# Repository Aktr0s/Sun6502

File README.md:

# Sun6502 Hobby Computer

## My first try at electonics. Wish me luck.

# Memory Map:

| Address Range   | Size   | Description        |
|-----------------|--------|--------------------|
| `$0000-$7FFF`   | 32KB   | RAM                |
| `$8000-$83FF`   | 1KB    | VIA #1             |
| `$8400-$87FF`   | 1KB    | UART               |
| `$8800-$8BFF`   | 1KB    | VIA #2             |
| `$8C00-$8FFF`   | 1KB    | Unused             |
| `$9000-$BFFF`   | 12KB   | Expansion Port     |
| `$C000-$FFFF`   | 16KB   | ROM                |

> **Total:** 64KB

> **If you have a previous version of the board notice that UART and VIA #2 addresses are swaped around.**

## More Info:
While VIA's and UART have 1KB they only use first needed bits.

VIA#2 Port (Expansion) does not have CE/ signal but Bus Expansion Port does.

It should be compatible with Ben's Breadboard 6502 but you **HAVE** to change memory adressess since the memory map is different as well as elements connected to VIA

### The project took inspiration from:
* Ben Eater Breadboard 6502 Computer
* PE6502 by Putnam Electronics

> [!NOTE]
> This project has been tested and is confirmed to work.

> [!CAUTION]
> Do NOT use 74LS series TTL chips. It messes up logic and memory.
> Use 74HC series CMOS chips! If somewhere on PCB or schematic there is a mention of TTL chips, ignore them and use CMOS chips!

## Software:

Software for this computer is based on 
* [msbasic](https://github.com/mist64/msbasic), licensed under the 2-clause BSD license.

* As well as it's modified version by [Ben Eater](https://github.com/beneater/msbasic).

Original README files are in "msbasic_for_sun6502" folder.

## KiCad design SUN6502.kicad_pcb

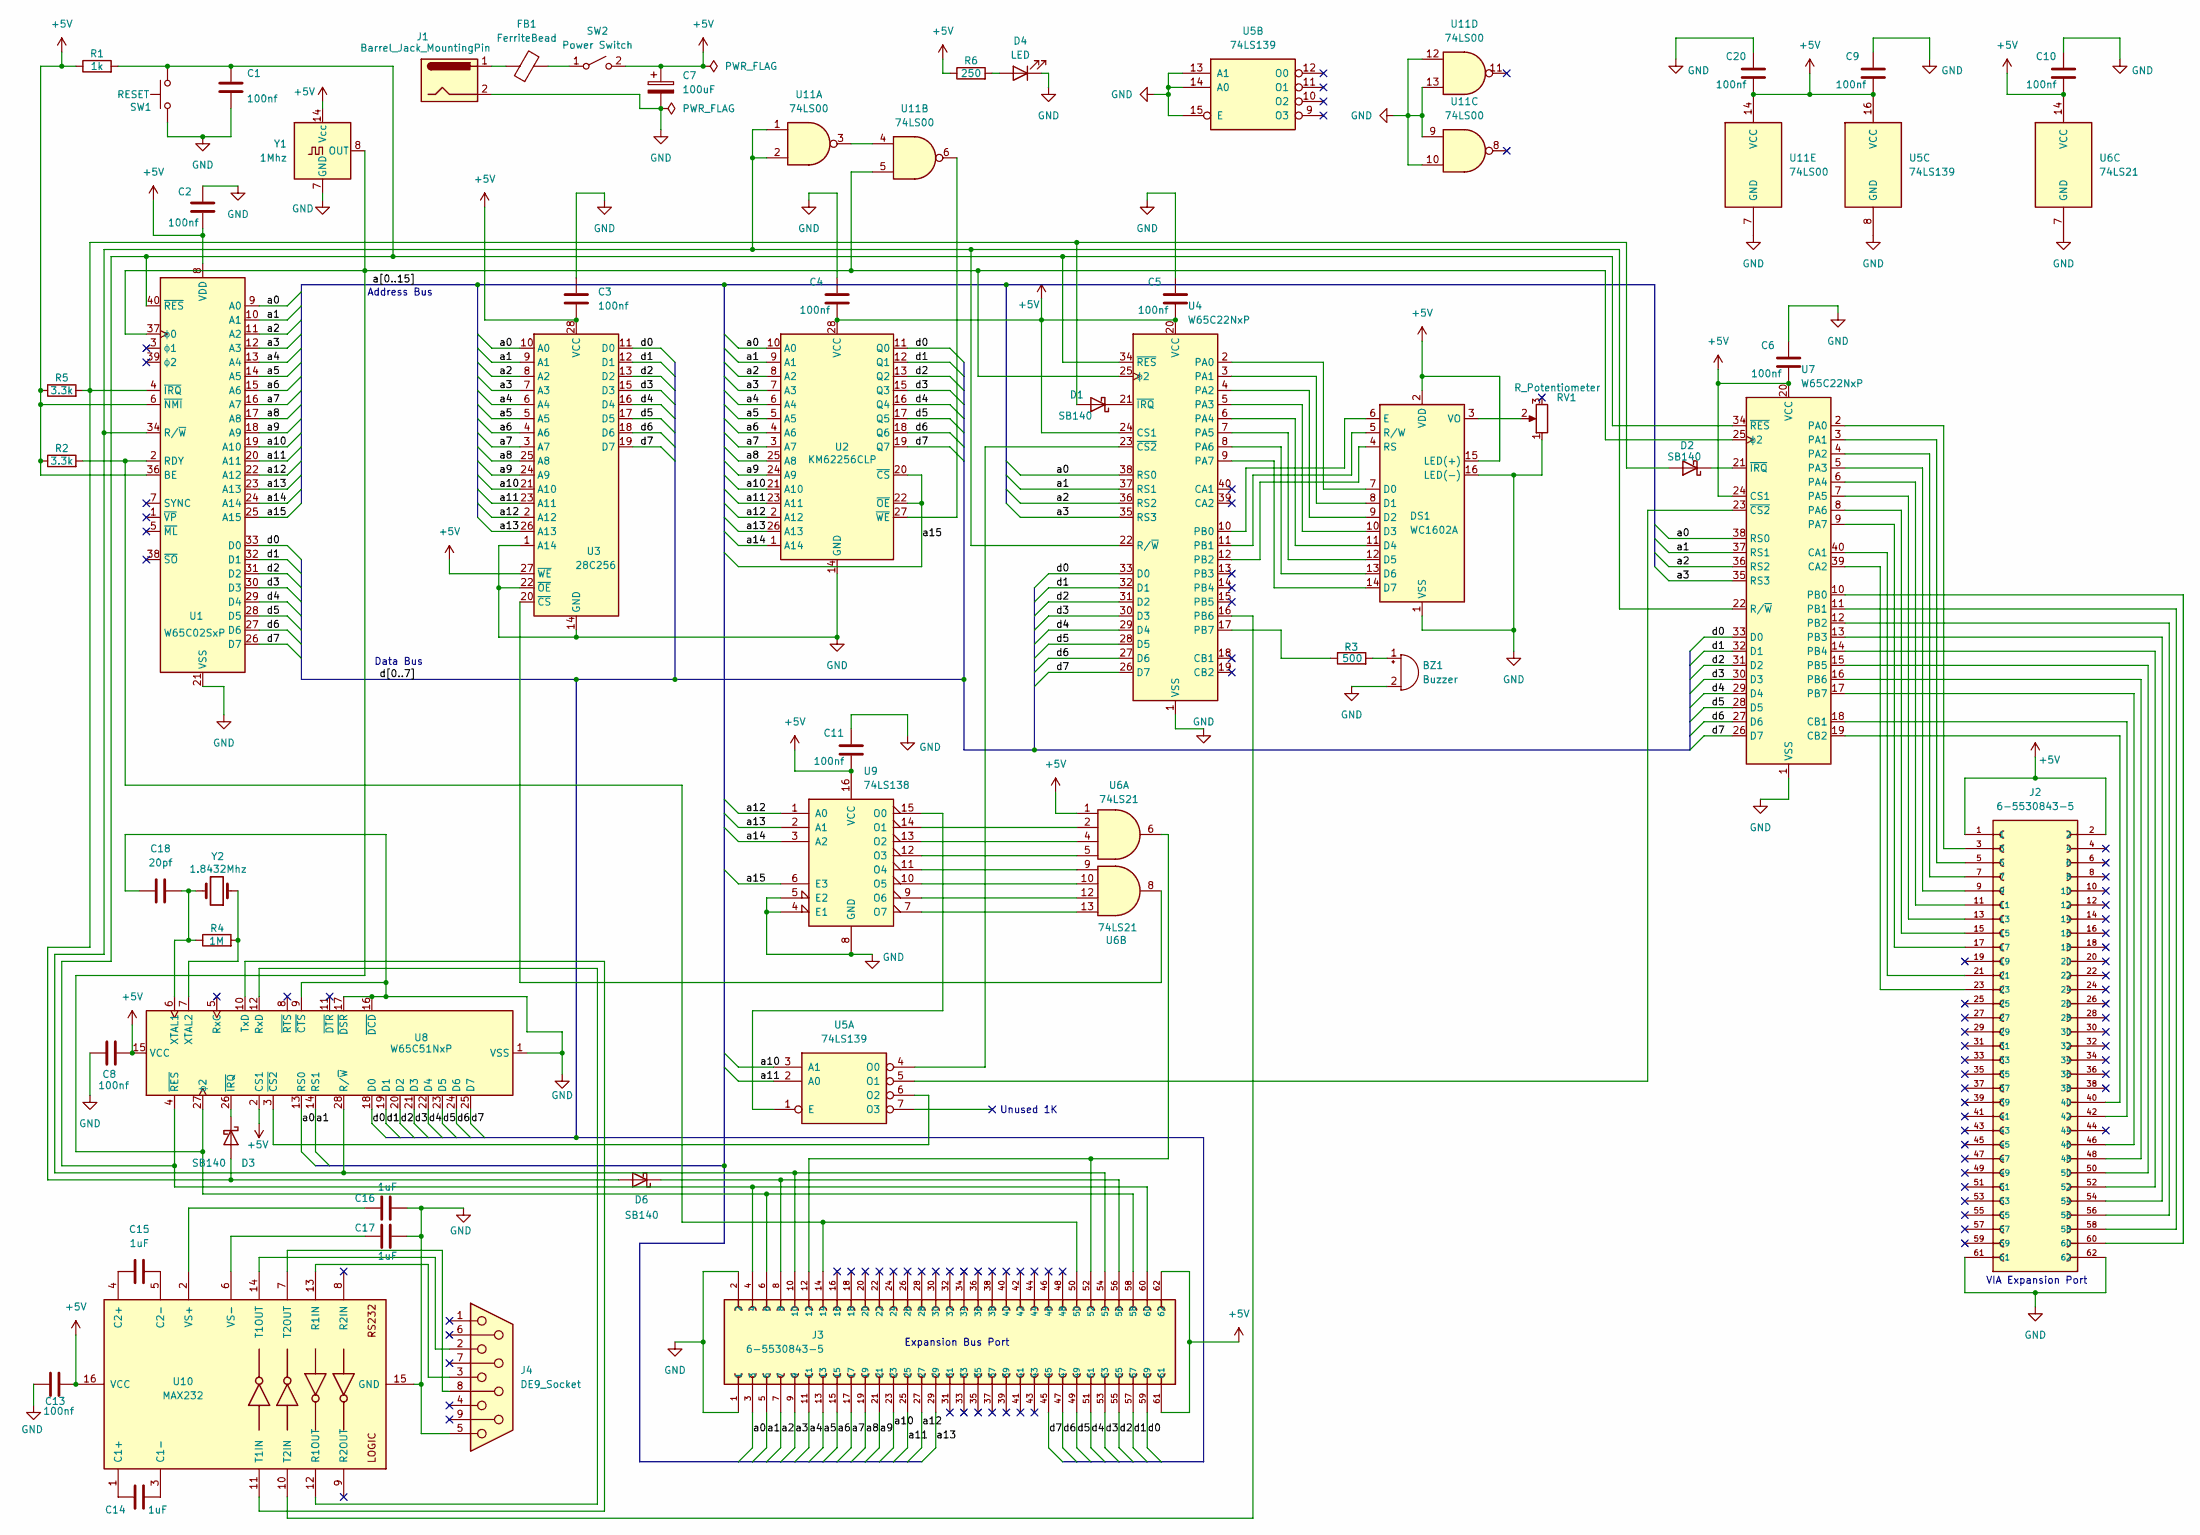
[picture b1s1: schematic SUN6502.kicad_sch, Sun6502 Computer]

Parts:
BZ1: Buzzer; Buzzer_TDK_PS1240P02BT_D12.2mm_H6.5mm
C1, C2, C3, C4, C5, C6, C8, C9, C10, C11, C13: 100nf; C_Disc_D5.0mm_W2.5mm_P5.00mm
C7: 100uF; CP_Radial_D6.3mm_P2.50mm
C14, C15, C16, C17: 1uF; C_Disc_D5.0mm_W2.5mm_P5.00mm
C18: 20pf; C_Disc_D5.0mm_W2.5mm_P5.00mm
C20: 100nf; C_Disc_D4.7mm_W2.5mm_P5.00mm
D1, D2, D3, D6: SB140; D_DO-41_SOD81_P10.16mm_Horizontal
D4: LED; LED_D5.0mm
DS1: WC1602A
FB1: FerriteBead; LairdTech_28C0236-0JW-10
J1: Barrel_Jack_MountingPin; BarrelJack_Horizontal
J2, J3: 6-5530843-5; TE_6-5530843-5
J4: DE9_Socket; DSUB-9_Socket_Horizontal_P2.77x2.84mm_EdgePinOffset7.70mm_H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
R1: 1k; R_Axial_DIN0207_L6.3mm_D2.5mm_P15.24mm_Horizontal
R2, R5: 3.3k; R_Axial_DIN0207_L6.3mm_D2.5mm_P15.24mm_Horizontal
R3: 500; R_Axial_DIN0207_L6.3mm_D2.5mm_P15.24mm_Horizontal
R4: 1M; R_Axial_DIN0207_L6.3mm_D2.5mm_P15.24mm_Horizontal
R6: 250; R_Axial_DIN0207_L6.3mm_D2.5mm_P10.16mm_Horizontal
RV1: R_Potentiometer; Potentiometer_Alps_RK09K_Single_Vertical
SW1: RESET; SW_PUSH_6mm_H5mm
SW2: Power Switch; 2MS6T1B3M2QES
U1: W65C02SxP; DIP-40_W15.24mm_Socket_LongPads
U2: KM62256CLP; DIP-28_W15.24mm_Socket_LongPads
U3: 28C256; DIP_Socket-28_W11.9_W12.7_W15.24_W17.78_W18.5_3M_228-1277-0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
U4, U7: W65C22NxP; DIP-40_W15.24mm_Socket_LongPads
U5: 74LS139; DIP-16_W7.62mm_Socket_LongPads
U6: 74LS21; DIP-14_W7.62mm_Socket_LongPads
U8: W65C51NxP; DIP-28_W15.24mm_Socket_LongPads
U9: 74LS138; DIP-16_W7.62mm_Socket_LongPads
U10: MAX232; DIP-16_W7.62mm_Socket_LongPads
U11: 74LS00; DIP-14_W7.62mm_Socket_LongPads
Y1: 1Mhz; Oscillator_DIP-14
Y2: 1.8432Mhz; Crystal_HC49-U_Vertical

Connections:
+5V: C2.2, C3.2, C4.2, C5.2, C6.2, C7.1, C8.2, C9.2, C10.2, C11.2, C13.2, C20.2, DS1.2 (VDD), DS1.15 (LED(+)), J2.1, J2.2, J3.61, J3.62, R1.1, R2.1, R5.1, R6.1, SW2.2 (B), U1.6 (~NMI), U1.8 (VDD), U1.36 (BE), U2.28 (VCC), U3.27 (~WE), U3.28 (VCC), U4.20 (VCC), U4.24 (CS1), U5.16 (VCC), U6.1, U6.14 (VCC), U7.20 (VCC), U7.24 (CS1), U8.2 (CS1), U8.15 (VCC), U9.16 (VCC), U10.16 (VCC), U11.14 (VCC), Y1.14 (Vcc)
/a0: J3.3, U1.9 (A0), U2.10 (A0), U3.10 (A0), U4.38 (RS0), U7.38 (RS0), U8.13 (RS0)
/a1: J3.5, U1.10 (A1), U2.9 (A1), U3.9 (A1), U4.37 (RS1), U7.37 (RS1), U8.14 (RS1)
/a2: J3.7, U1.11 (A2), U2.8 (A2), U3.8 (A2), U4.36 (RS2), U7.36 (RS2)
/a3: J3.9, U1.12 (A3), U2.7 (A3), U3.7 (A3), U4.35 (RS3), U7.35 (RS3)
/a4: J3.11, U1.13 (A4), U2.6 (A4), U3.6 (A4)
/a5: J3.13, U1.14 (A5), U2.5 (A5), U3.5 (A5)
/a6: J3.15, U1.15 (A6), U2.4 (A6), U3.4 (A6)
/a7: J3.17, U1.16 (A7), U2.3 (A7), U3.3 (A7)
/a8: J3.19, U1.17 (A8), U2.25 (A8), U3.25 (A8)
/a9: J3.21, U1.18 (A9), U2.24 (A9), U3.24 (A9)
/a10: J3.23, U1.19 (A10), U2.21 (A10), U3.21 (A10), U5.3 (A1)
/a11: J3.25, U1.20 (A11), U2.23 (A11), U3.23 (A11), U5.2 (A0)
/a12: J3.27, U1.22 (A12), U2.2 (A12), U3.2 (A12), U9.1 (A0)
/a13: J3.29, U1.23 (A13), U2.26 (A13), U3.26 (A13), U9.2 (A1)
/a14: U1.24 (A14), U2.1 (A14), U9.3 (A2)
/a15: U1.25 (A15), U2.20 (~CS), U2.22 (~OE), U9.6 (E3)
/d0: J3.59, U1.33 (D0), U2.11 (Q0), U3.11 (D0), U4.33 (D0), U7.33 (D0), U8.18 (D0)
/d1: J3.57, U1.32 (D1), U2.12 (Q1), U3.12 (D1), U4.32 (D1), U7.32 (D1), U8.19 (D1)
/d2: J3.55, U1.31 (D2), U2.13 (Q2), U3.13 (D2), U4.31 (D2), U7.31 (D2), U8.20 (D2)
/d3: J3.53, U1.30 (D3), U2.15 (Q3), U3.15 (D3), U4.30 (D3), U7.30 (D3), U8.21 (D3)
/d4: J3.51, U1.29 (D4), U2.16 (Q4), U3.16 (D4), U4.29 (D4), U7.29 (D4), U8.22 (D4)
/d5: J3.49, U1.28 (D5), U2.17 (Q5), U3.17 (D5), U4.28 (D5), U7.28 (D5), U8.23 (D5)
/d6: J3.47, U1.27 (D6), U2.18 (Q6), U3.18 (D6), U4.27 (D6), U7.27 (D6), U8.24 (D6)
/d7: J3.45, U1.26 (D7), U2.19 (Q7), U3.19 (D7), U4.26 (D7), U7.26 (D7), U8.25 (D7)
GND: BZ1.2 (-), C1.2, C2.1, C3.1, C4.1, C5.1, C6.1, C7.2, C8.1, C9.1, C10.1, C11.1, C13.1, C16.2, C17.2, C18.1, C20.1, D4.1 (K), DS1.1 (VSS), DS1.16 (LED(-)), J1.2, J2.61, J2.62, J3.1, J3.2, J4.5, RV1.1, SW1.1, U1.21 (VSS), U2.14 (GND), U3.1 (A14), U3.14 (GND), U3.22 (~OE), U4.1 (VSS), U5.8 (GND), U5.13 (A1), U5.14 (A0), U5.15 (E), U6.7 (GND), U7.1 (VSS), U8.1 (VSS), U8.9 (~CTS), U8.16 (~DCD), U8.17 (~DSR), U9.4 (E1), U9.5 (E2), U9.8 (GND), U10.15 (GND), U11.7 (GND), U11.9, U11.10, U11.12, U11.13, Y1.7 (GND)
unnamed: BZ1.1 (+), R3.2
unnamed: D1.2 (A), D2.2 (A), D3.2 (A), D6.2 (A), R5.2, U1.4 (~IRQ)
unnamed: D1.1 (K), U4.21 (~IRQ)
unnamed: D2.1 (K), U7.21 (~IRQ)
unnamed: D3.1 (K), U8.26 (~IRQ)
unnamed: D4.2 (A), R6.2
unnamed: D6.1 (K), J3.8, J3.56
unnamed: DS1.7 (D0), U4.2 (PA0)
unnamed: DS1.8 (D1), U4.3 (PA1)
unnamed: DS1.9 (D2), U4.4 (PA2)
unnamed: DS1.10 (D3), U4.5 (PA3)
unnamed: DS1.11 (D4), U4.6 (PA4)
unnamed: DS1.12 (D5), U4.7 (PA5)
unnamed: DS1.13 (D6), U4.8 (PA6)
unnamed: DS1.14 (D7), U4.9 (PA7)
unnamed: DS1.6 (E), U4.10 (PB0)
unnamed: DS1.4 (RS), U4.12 (PB2)
unnamed: DS1.5 (R/W), U4.11 (PB1)
unnamed: DS1.3 (VO), RV1.2
unnamed: FB1.1, J1.1
unnamed: J3.12, J3.52, U6.6
unnamed: FB1.2, SW2.1 (A)
unnamed: J3.14, J3.50, R2.2, U1.2 (RDY)
unnamed: J3.10, J3.54, U1.34 (R/~W), U4.22 (R/~W), U7.22 (R/~W), U8.28 (R/~W), U11.1, U11.2
unnamed: C1.1, J3.4, J3.60, R1.2, SW1.2, U1.40 (~RES), U4.34 (~RES), U7.34 (~RES), U8.4 (~RES)
unnamed: J3.6, J3.58, U1.37 (ϕ0), U4.25 (ϕ2), U7.25 (ϕ2), U8.27 (ϕ2), U11.5, Y1.8 (OUT)
unnamed: U2.27 (~WE), U11.6
unnamed: U3.20 (~CS), U6.8
unnamed: R3.1, U4.17 (PB7)
unnamed: U4.23 (~CS2), U5.4 (O0)
unnamed: U5.1 (E), U9.15 (O0)
unnamed: U5.5 (O1), U7.23 (~CS2)
unnamed: U5.6 (O2), U8.3 (~CS2)
unnamed: J2.21, U7.40 (CA1)
unnamed: J2.23, U7.39 (CA2)
unnamed: J2.42, U7.18 (CB1)
unnamed: J2.40, U7.19 (CB2)
unnamed: J2.3, U7.2 (PA0)
unnamed: J2.5, U7.3 (PA1)
unnamed: J2.7, U7.4 (PA2)
unnamed: J2.9, U7.5 (PA3)
unnamed: J2.11, U7.6 (PA4)
unnamed: J2.13, U7.7 (PA5)
unnamed: J2.15, U7.8 (PA6)
unnamed: J2.17, U7.9 (PA7)
unnamed: J2.60, U7.10 (PB0)
unnamed: J2.58, U7.11 (PB1)
unnamed: J2.56, U7.12 (PB2)
unnamed: J2.54, U7.13 (PB3)
unnamed: J2.52, U7.14 (PB4)
unnamed: J2.50, U7.15 (PB5)
unnamed: J2.48, U7.16 (PB6)
unnamed: J2.46, U7.17 (PB7)
unnamed: C18.2, R4.1, U8.6 (XTAL1), Y2.2
unnamed: R4.2, U8.7 (XTAL2), Y2.1
unnamed: U6.2, U9.14 (O1)
unnamed: U6.4, U9.13 (O2)
unnamed: U6.5, U9.12 (O3)
unnamed: U6.9, U9.11 (O4)
unnamed: U6.10, U9.10 (O5)
unnamed: U6.12, U9.9 (O6)
unnamed: U6.13, U9.7 (O7)
unnamed: C14.1, U10.1 (C1+)
unnamed: C14.2, U10.3 (C1-)
unnamed: C15.1, U10.4 (C2+)
unnamed: C15.2, U10.5 (C2-)
unnamed: J4.3, U10.13 (R1IN)
unnamed: U8.12 (RxD), U10.12 (R1OUT)
unnamed: U8.10 (TxD), U10.11 (T1IN)
unnamed: J4.2, U10.14 (T1OUT)
unnamed: U4.16 (PB6), U10.10 (T2IN)
unnamed: J4.8, U10.7 (T2OUT)
unnamed: C16.1, U10.2 (VS+)
unnamed: C17.1, U10.6 (VS-)
unnamed: U11.3, U11.4

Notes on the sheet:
Unused 1K
Address Bus
VIA Expansion Port
Expansion Bus Port
Data Bus

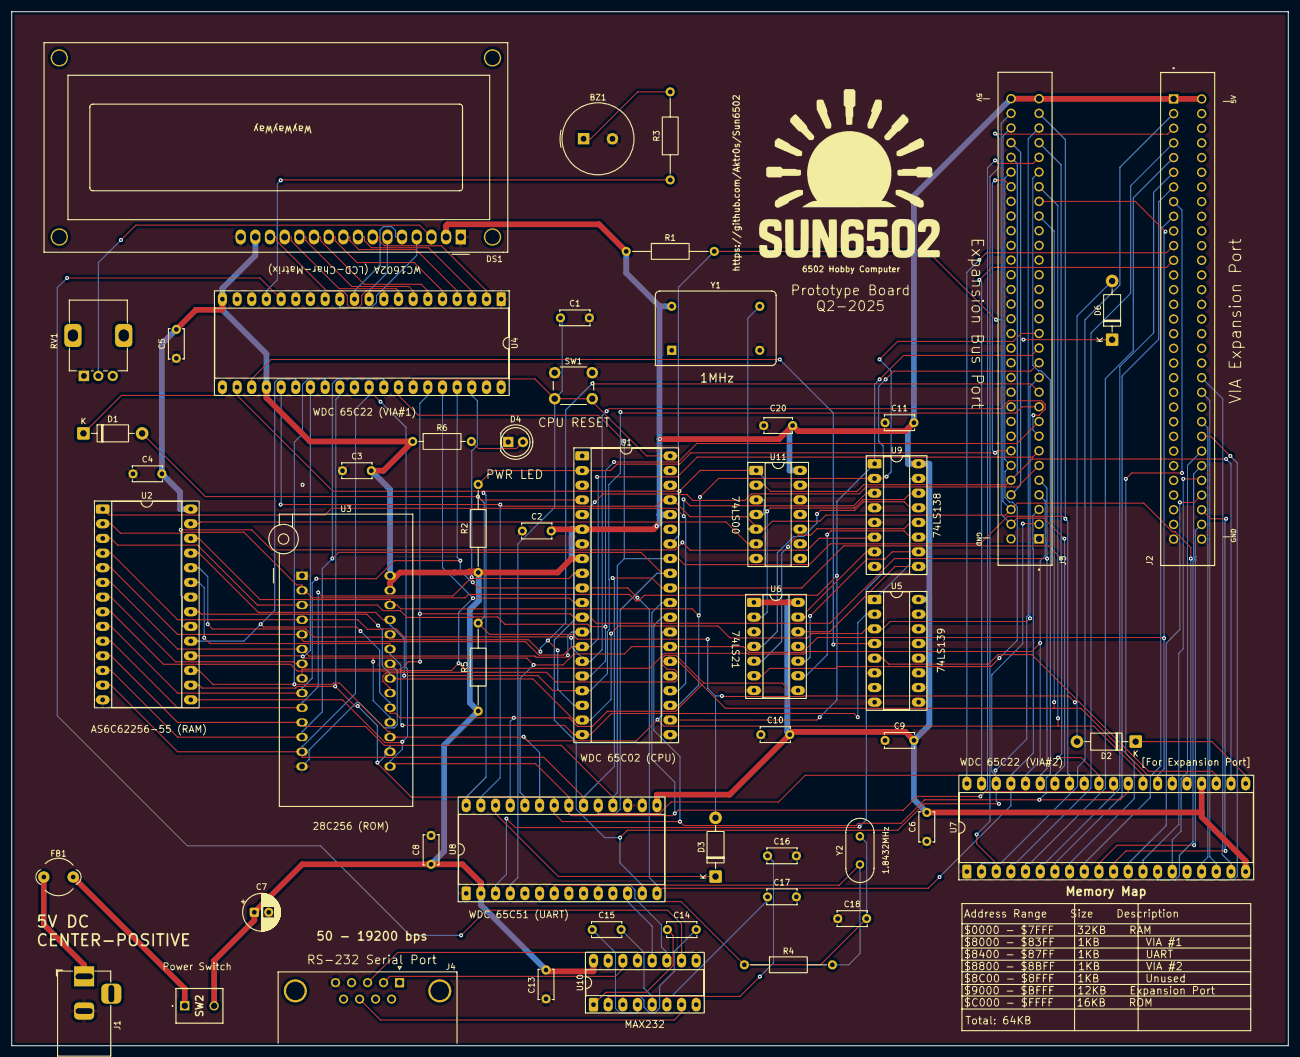
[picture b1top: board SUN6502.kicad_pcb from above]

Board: 2 copper layers, 221.0 x 179.0 mm, 52 parts (0 on the bottom side), 101 nets.

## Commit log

2025-05-27 inicial commit
2025-06-02 updates, removed backup files
2025-06-02 Remove backup files from repo and stop tracking
2025-06-06 updates, schematic more or less ready for pcb mapping
2025-06-08 pcb layout done
2025-06-11 updates, changed ROM socket into ZIF
2025-06-13 pcb changed to 2 layers, CTR Added
2025-06-17 small changes
2025-07-02 Add files via upload
    Added bios bin file and PNG schematic
2025-07-07 updates, board works
2026-03-20 Updated warnings about chip usage in the README.
2026-06-10 fixes, changed intro message and prompt. changed defines from eater to sun6502
